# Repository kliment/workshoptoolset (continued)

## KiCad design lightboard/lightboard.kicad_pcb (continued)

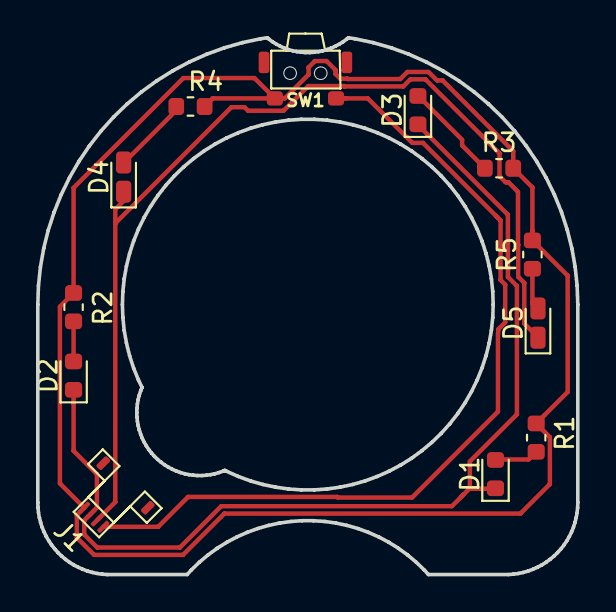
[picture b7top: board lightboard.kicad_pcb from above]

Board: 2 copper layers, 30.0 x 29.8 mm, 12 parts (0 on the bottom side), 9 nets.

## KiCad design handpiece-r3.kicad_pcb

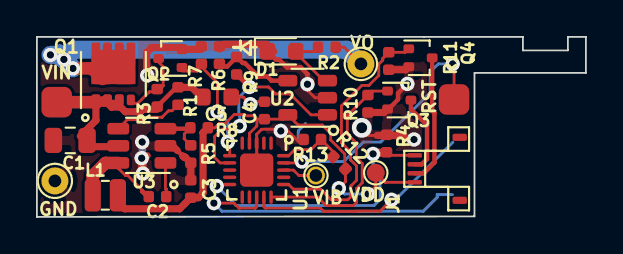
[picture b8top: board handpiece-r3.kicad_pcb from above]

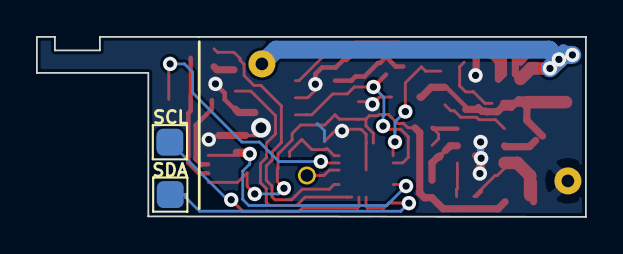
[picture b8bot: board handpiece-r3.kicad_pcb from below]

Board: 2 copper layers, 30.5 x 10.0 mm, 36 parts (2 on the bottom side), 23 nets.

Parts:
C1: 4.7u; C_0805_2012Metric
C2, C4: 0.1u; C_0402_1005Metric
C3: 10u; C_0402_1005Metric
C5: 4.7u; C_0603_1608Metric
D1: ESD5Z5.0VC; LED_0603_1608Metric
GND: TestPoint; TestPoint_THTPad_D1.5mm_Drill0.7mm
J1: Conn_01x04; FPC_4_0.5-THD0509-04CL-GF
L1: CPY160808T-4R7M-NP; INDUCTOR_2x1.6x1mm
Q1: DMP3007SCG; VSON-8_3.3x3.3mm_P0.65mm_NexFET
Q2, Q3, Q4: 2SK3019; SOT-416
R1: 100k; R_0402_1005Metric
R2, R3, R4, R7, R8, R10, R11: 10k; R_0402_1005Metric
R5: 1.91k; R_0402_1005Metric
R6: 1k; R_0402_1005Metric
R9: 49.9k; R_0402_1005Metric
R12, R13: R; R_0402_1005Metric
RST: TestPoint_Probe; TestPoint_Pad_D1.0mm
SCL: TestPoint; TestPoint_Pad_1.5x1.5mm
SDA: TestPoint; TestPoint_Pad_1.5x1.5mm
U1: ATTINY416-M; UQFN-20-1EP_3x3mm_P0.4mm_EP1.85x1.85mm
U2: GS8591-TR; SOT-23-5
U3: JW5026; TSOT-23-6
VDD: TestPoint_Probe; TestPoint_Pad_D1.0mm
VIB: TestPoint; TestPoint_THTPad_D1.5mm_Drill0.7mm
VIN: TestPoint; TestPoint_THTPad_D1.5mm_Drill0.7mm
VO: TestPoint; TestPoint_THTPad_D1.5mm_Drill0.7mm

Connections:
/ATEMP: R12.2, R13.1, U1.20
BTN: J1.4, R4.1, U1.10
GND: C1.2, C3.2, C4.2, C5.2, D1.1, GND.1, Q2.2, Q3.2, Q4.2, R4.2, R5.2, R6.1, R7.2, R10.2, R11.2, R13.2, U1.3, U2.2, U3.2
unnamed: C2.1, L1.2, U3.6
unnamed: C2.2, U3.1
unnamed: D1.2, R2.1, U2.3
unnamed: Q1.4, Q2.3, R3.2
unnamed: Q2.1, R7.1, U1.6
unnamed: Q3.1, R10.1, U1.15
unnamed: Q4.1, R11.1, U1.16
unnamed: R1.2, U3.4
unnamed: R5.1, R8.2, U3.3
unnamed: R6.2, R9.2, U2.4
unnamed: R9.1, U1.7, U2.1
unnamed: RST.1, U1.19
RED: J1.3, Q3.3
SCL: SCL.1, U1.14
SDA: SDA.1, U1.13
VDD: C3.1, C4.1, J1.1, L1.1, R8.1, R12.1, U1.4, U2.5, VDD.1
VIBR: U1.18, VIB.1
VIN: C1.1, C5.1, Q1.1, Q1.2, Q1.3, R1.1, R3.1, U3.5, VIN.1
VOUT: Q1.5, R2.2, VO.1
WHITE: J1.2, Q4.3

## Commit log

2019-11-14 Adding handpiece firmware
2019-11-14 Add soldering iron handpiece hardware
2019-11-14 Add soldering iron lightboard/stand
2019-11-14 Add usb charger and plug board
2019-11-14 Add microcontroller base board
2019-11-14 Add caches
2019-11-14 Add dimmer board
2019-11-14 add openscad files
2019-12-03 Format
2019-12-03 Add config.h for settings
2019-12-03 Clean up PID / numerics
2019-12-03 More cleanup
2019-12-03 Add gitignore
2019-12-03 Improve max duty cycle handling
2019-12-03 Comments
2019-12-04 Add constant current dimmer prototype design
2019-12-04 Change indent width to 4
2019-12-04 Clarify usage of REAL typedef
2019-12-04 Comment variables. Refactor time handling.
2019-12-04 Improve idle handling
2019-12-04 duty cycle must not be more than 100
2019-12-04 Make it easier to change the avrdude path
2019-12-04 Better range checking
2019-12-04 Rename LEDs
2019-12-21 Rename software folder: template -> handpiece
2019-12-21 Randomly distribute the FET switching over the 100 ms cycles
2019-12-21 Fix duty cycle distribution
2019-12-21 Make more variables non-volatile
2019-12-21 Make calctemp standalone and call it at a better point in the cycle
2019-12-21 Formatting
2019-12-21 Add sigma delta modulation to increase switching frequency
2019-12-21 Remove obsolete warning
2019-12-21 Remove debug flickering
2019-12-21 Cleanup, documentation
2019-12-21 static inline functions
2019-12-21 Remove volatile from duty declaration
2019-12-22 Turn off FET after sigma-delta
2019-12-22 Remove unused headers
2019-12-22 Clean up build system
2019-12-22 Forgot to rm gcc and add device
2019-12-22 Some fixes/deletes
2019-12-22 Build directories are order-only dependencies to prevent unnecessary rebuilds
2019-12-22 Put bin/hex files in base dir
2019-12-22 Remove attiny416 files
2019-12-22 gitignore, clang-format
2019-12-22 Do not ignore crt*.o files
2019-12-22 make datareg non-volatile
2019-12-22 Improve documentation
2019-12-22 Remove atmel_start files and just use system_init directly
2019-12-22 Move defaults to config.h
2019-12-23 Distribute initial start over a cycle, not a switching period. Configurable cycle length.
2019-12-27 Require 700 ms press to turn on the heat
2019-12-27 Add code for talking to the radio
2019-12-28 Wait for 200 ms before turning the iron off
2020-10-23 Add cheaty dimmer
